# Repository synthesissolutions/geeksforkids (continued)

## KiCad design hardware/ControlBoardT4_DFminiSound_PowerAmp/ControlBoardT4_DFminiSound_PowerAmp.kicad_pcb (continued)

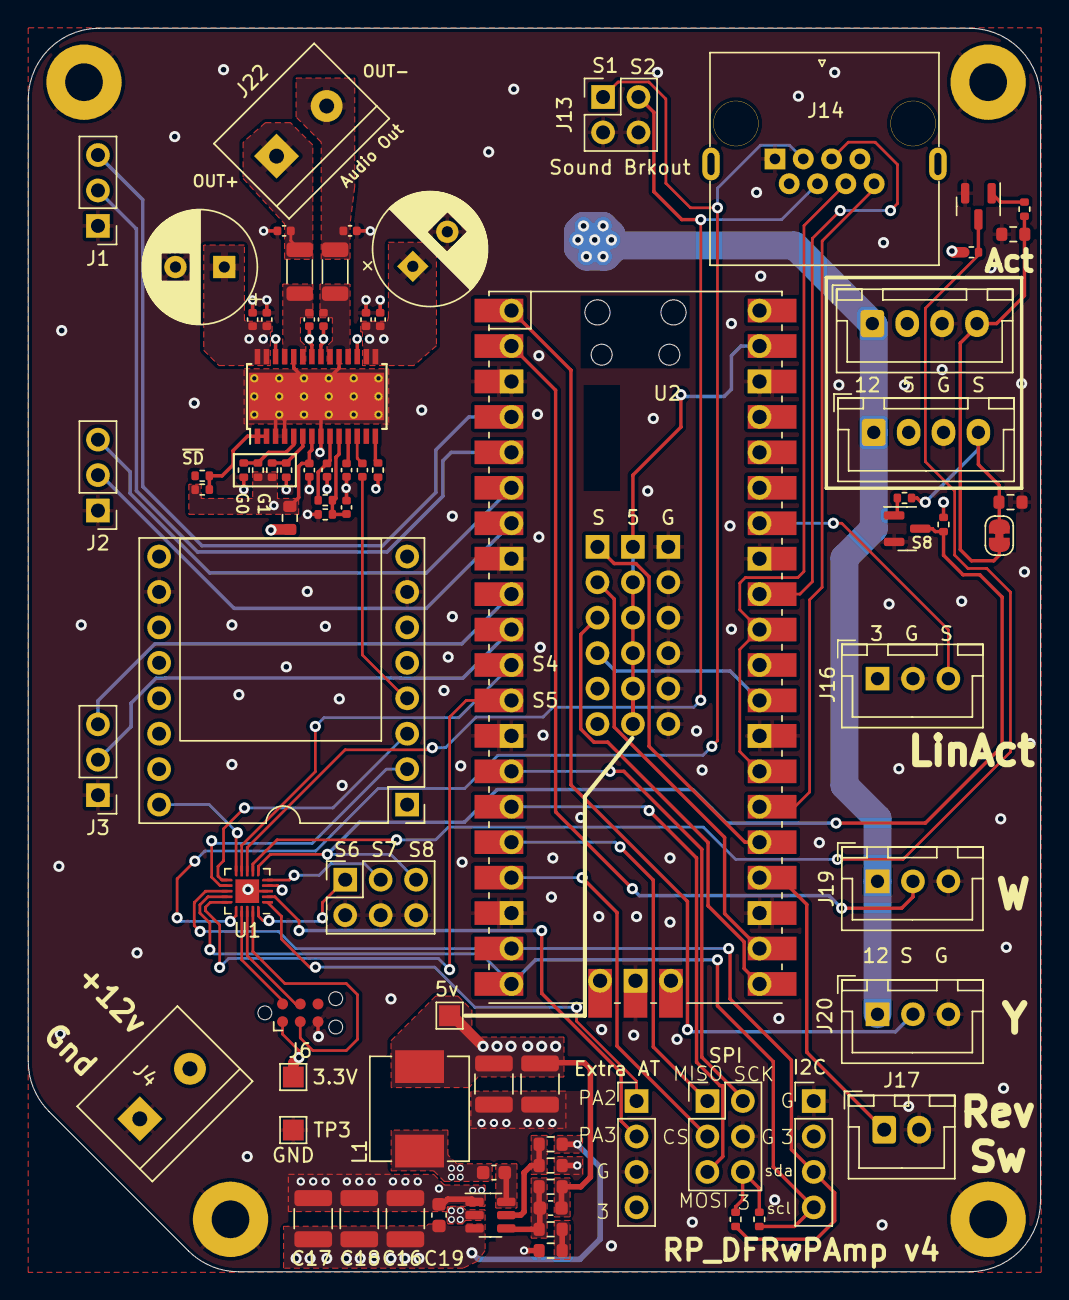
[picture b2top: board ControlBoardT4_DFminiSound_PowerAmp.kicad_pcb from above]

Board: 4 copper layers, 72.6 x 89.1 mm, 85 parts (0 on the bottom side), 68 nets.

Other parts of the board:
5v: 5V; TestPoint_Pad_1.5x1.5mm

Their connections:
+5V: 5v.1; also elsewhere on the board

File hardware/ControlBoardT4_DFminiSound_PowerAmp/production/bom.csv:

Designator,Footprint,Quantity,Value,LCSC Part #
"C1, C4, C5",0402,3,1uF,C1518208
"C10, C9",0402,2,0.47uF,C437527
"C11, C12, C15, C8",0402,4,1nF,C106205
"C13, C6",CP_Radial_D8.0mm_P3.50mm,2,100uF,C112510
"C14, C7",0402,2,100nF,C105882
"C16, C17, C18",1210,3,10µF,C380537
"C19, C20",0603,2,0.1µF,C77055
"C2, C3",0402,2,0.68uF,C113784
C21,0603,1,150pF,C527999
"C22, C23",1210,2,47µF,C77101
"FB1, FB2",1206,2,120Ohm@100MHz,C3011219
J15,PinSocket_1x06_P2.54mm_Vertical,1,RC_Signal,
J18,PinSocket_1x06_P2.54mm_Vertical,1,RC_5v,
J19,JST_XH_B3B-XH-A_1x03_P2.54mm_Vertical,1,M5 SCL,
J21,PinSocket_1x06_P2.54mm_Vertical,1,RC_GND,
L1,L_Sunlord_MWSA0603S,1,10µH,C132141
"Q1, Q2",SOT-23,2,2N7002,C8545
"R1, R12, R13, R17, R18, R8, R9",0402,7,100k,C60491
"R10, R11, R14",0402,3,0,C17168
R15,0603,1,10R,C22859
"R16, R5, R6",0402,3,1k,C11702
"R2, R4",0402,2,4.7k,C25900
R21,0603,1,100kΩ 1%,C25803
"R22, R3, R7",0603,3,13.3kΩ 1%,C25952
R23,0603,1,240Ω 1%,C23350
U1,VQFN-20-1EP_3x3mm_P0.4mm_EP1.7x1.7mm,1,ATtiny1616-M,C507118
U3,HTSSOP-28-1EP_4.4x9.7mm_P0.65mm_EP3.4x9.5mm_Mask2.4x6.17mm_ThermalVias,1,TPA3110D2,C30132
U4,SOT-23-6,1,TPS54302,C311983

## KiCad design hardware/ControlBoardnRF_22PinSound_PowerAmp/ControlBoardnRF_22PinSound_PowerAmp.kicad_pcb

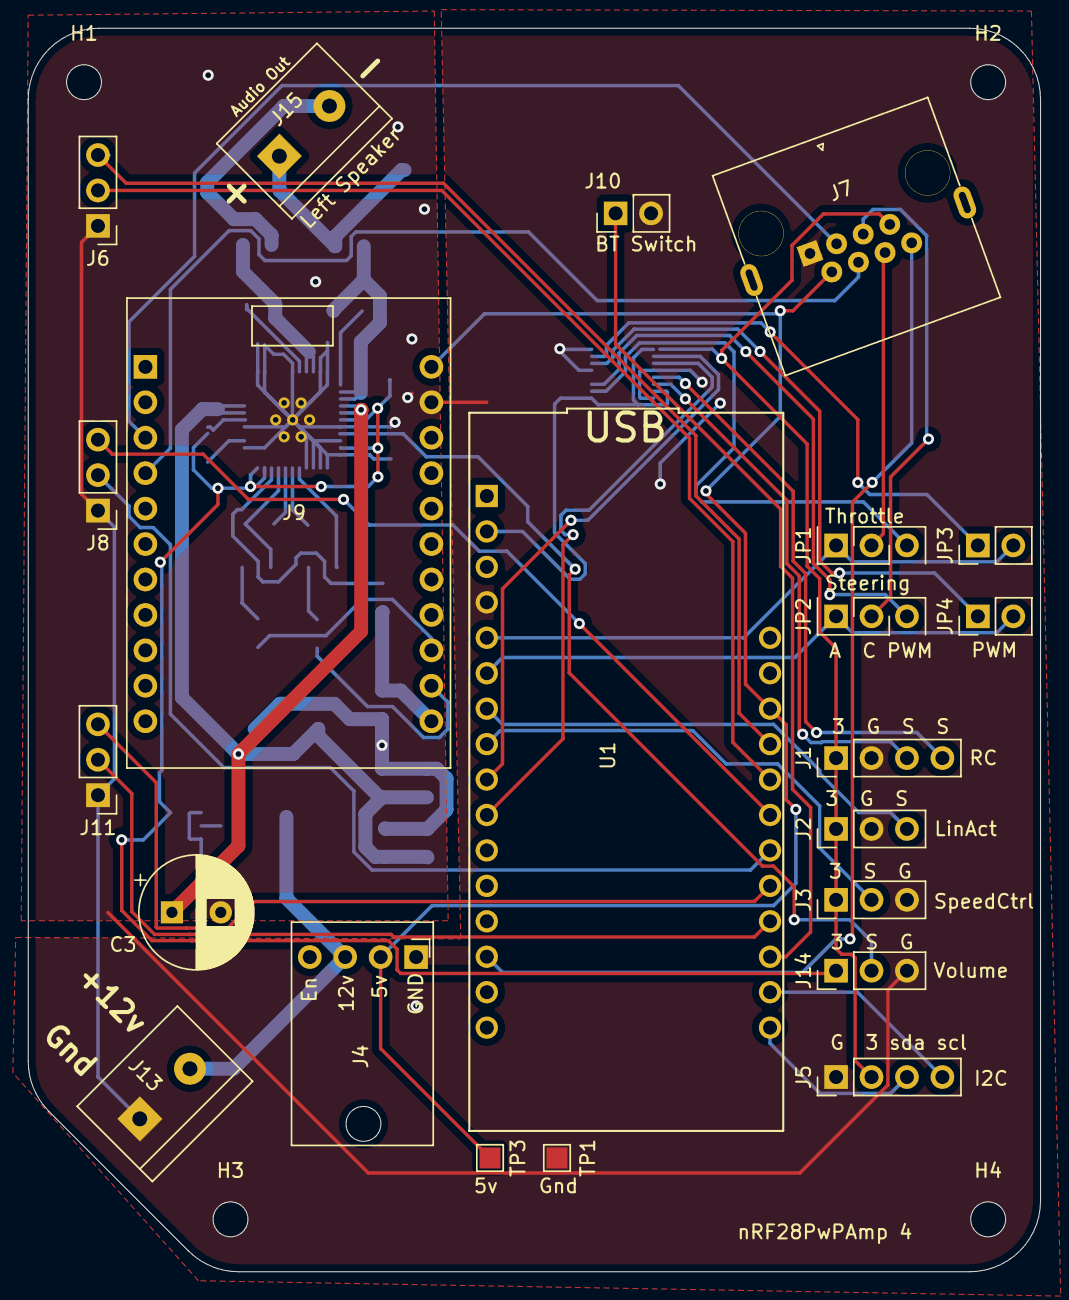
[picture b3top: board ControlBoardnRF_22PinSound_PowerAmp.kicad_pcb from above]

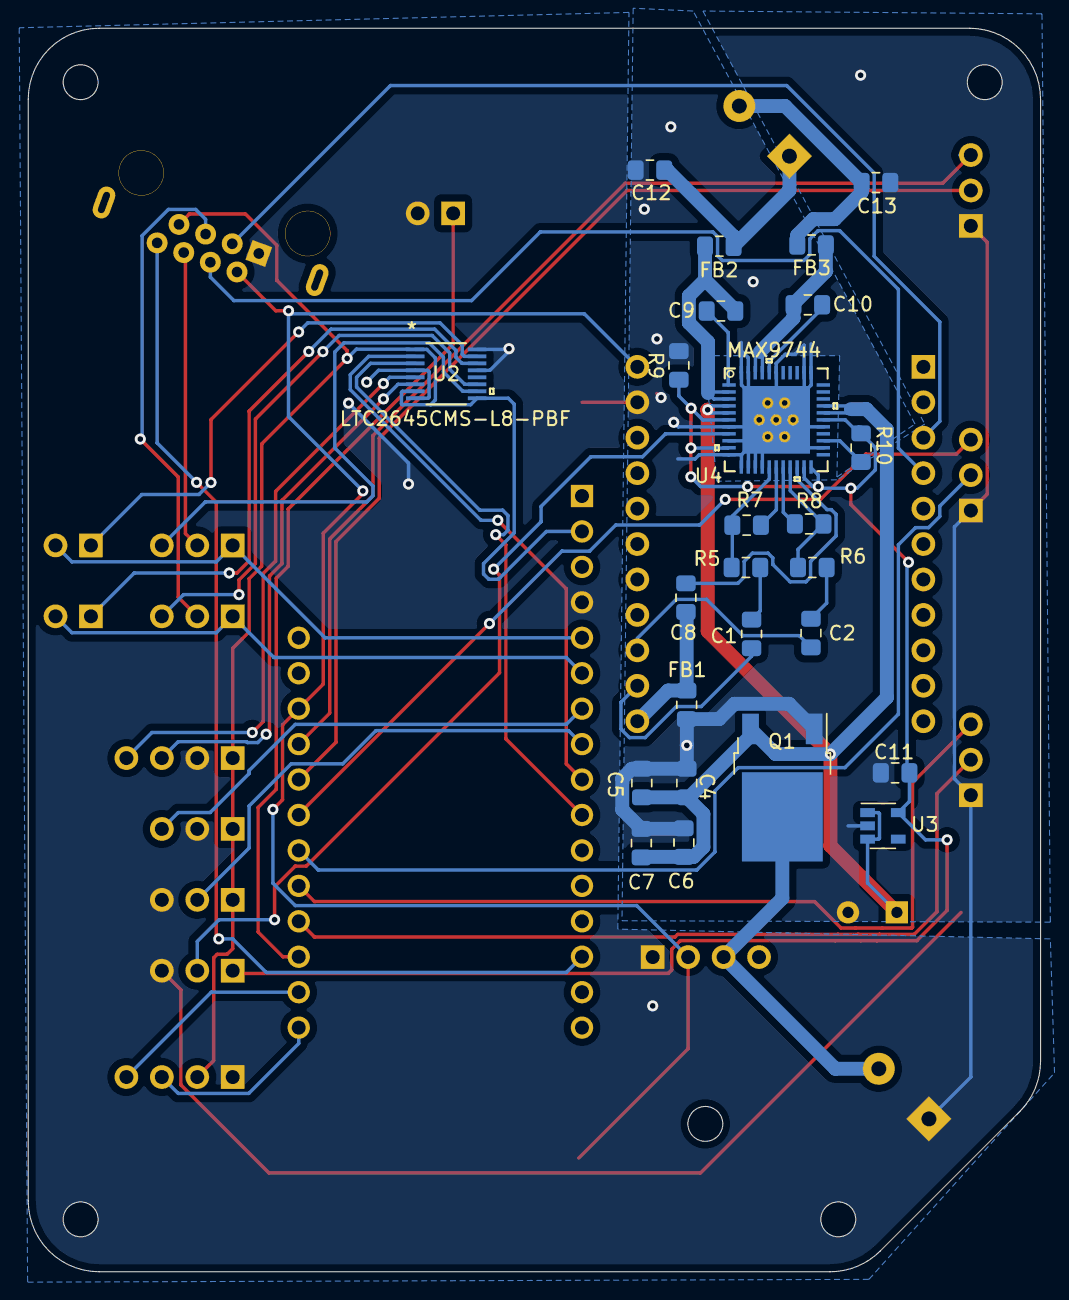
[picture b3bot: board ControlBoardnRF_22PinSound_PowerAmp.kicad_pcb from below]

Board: 2 copper layers, 72.6 x 89.1 mm, 51 parts (25 on the bottom side), 50 nets.

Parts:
C1, C2: 0.47µF; C_0805_2012Metric_Pad1.15x1.40mm_HandSolder
C3: 470µF; CP_Radial_D8.0mm_P3.50mm
C4, C5, C11: 10µF; C_0805_2012Metric_Pad1.15x1.40mm_HandSolder
C6, C7, C9, C10: 0.1µF; C_0805_2012Metric_Pad1.15x1.40mm_HandSolder
C8: 2.2µF; C_0805_2012Metric_Pad1.15x1.40mm_HandSolder
C12, C13: 470pF; C_0805_2012Metric_Pad1.15x1.40mm_HandSolder
FB1, FB2, FB3: MPZ2012S221AT00; L_0805_2012Metric_Pad1.15x1.40mm_HandSolder
H1, H2, H3, H4: MountingHole; MountingHole_2.5mm
J1: RC; PinHeader_1x04_P2.54mm_Vertical
J2: LinAct; PinHeader_1x03_P2.54mm_Vertical
J3: SpeedCtrl; PinHeader_1x03_P2.54mm_Vertical
J4: Power Input; AdaFruit_MPM3610
J5: I2C; PinHeader_1x04_P2.54mm_Vertical
J6: Left_M1; PinHeader_1x03_P2.54mm_Vertical
J7: 8P8C; RJ45_x08_Tab_Up
J8: Right_M2; PinHeader_1x03_P2.54mm_Vertical
J9: 22Pin_FXSound; FXSound_2x11_P2.54mm_Short
J10: BT Switch; PinHeader_1x02_P2.54mm_Vertical
J11: LinAct_M3; PinHeader_1x03_P2.54mm_Vertical
J13: Main Power; TerminalBlock_bornier-2_P5.08mm
J14: Volume; PinHeader_1x03_P2.54mm_Vertical
J15: Left Speaker; TerminalBlock_bornier-2_P5.08mm
JP1: Throttle Jumper; PinHeader_1x03_P2.54mm_Vertical
JP2: Steering Jumper; PinHeader_1x03_P2.54mm_Vertical
JP3: LTC Throttle Jumper; PinHeader_1x02_P2.54mm_Vertical
JP4: LTC Steering Jumper; PinHeader_1x02_P2.54mm_Vertical
Q1: AOD417; TO-252-2pin3D
R5, R6, R7, R8: 20K; R_0805_2012Metric_Pad1.15x1.40mm_HandSolder
R9, R10: 10K; R_0805_2012Metric_Pad1.15x1.40mm_HandSolder
TP1: Gnd; TestPoint_Pad_1.5x1.5mm
TP3: 5v; TestPoint_Pad_1.5x1.5mm
U1: Feather_nRF52840
U2: LTC2645CMS-L8-PBF
U3: AP2112K-3.3; SOT-23-5
U4: MAX9744; max9744eth&plus_Mod

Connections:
+3.3VP: C11.1, J14.1, R9.1, R10.2, U3.5, U4.6, U4.10, U4.21, U4.22, U4.28
+3V3: J1.1, J2.1, J3.1, J5.2, J7.7, U1.2, U2.1, U2.7, U2.9
+5V: J4.2, J7.2, J9.2, TP3.1, U1.26
+12V: J4.3, J13.2, Q1.3
ActiveSW: J7.8, U1.14
BT_Switch: J10.1, U1.19
GND: C3.2, C4.1, C5.1, C6.1, C7.1, C11.2, C12.1, C13.2, FB1.2, J1.2, J2.2, J3.3, J4.1, J5.1, J6.1, J7.1, J8.1, J9.4, J10.2, J11.1, J13.1, J14.3, Q1.1, R9.2, TP1.1, U1.4, U2.4, U2.8, U2.13, U2.16, U3.2, U4.7, U4.9, U4.11, U4.12, U4.13, U4.14, U4.15, U4.24, U4.27, U4.34, U4.35, U4.39, U4.43, U4.44, U4.45
GNDA: C8.2, FB1.1, J9.22
I2C_SCL: J5.4, U1.18
I2C_SDA: J5.3, U1.17
LeftIN: C1.2, J9.20
Left_DIR: J6.2, U1.24
Left_PWM: J6.3, U1.25
LinAct_DIR: J11.2, U1.20
LinAct_PWM: J11.3, U1.21
LinAct_Position: J2.3, U1.7
unnamed: C1.1, R5.2
unnamed: C2.1, R6.2
unnamed: C3.1, C4.2, C5.2, C6.2, C7.2, Q1.2, U3.1, U3.3, U4.4, U4.5, U4.29, U4.30
unnamed: C8.1, U4.20
unnamed: C9.1, FB2.1, U4.2, U4.3
unnamed: C9.2, U4.1
unnamed: C10.1, FB3.1, U4.41, U4.42
unnamed: C10.2, U4.40
unnamed: C12.2, FB2.2, J15.1
unnamed: C13.1, FB3.2, J15.2
unnamed: J7.5, JP2.2
unnamed: J7.6, JP1.2
unnamed: J14.2, U4.8
unnamed: JP3.1, U2.15
unnamed: JP4.1, U2.14
unnamed: R5.1, R7.2, U4.16
unnamed: R6.1, R8.2, U4.19
unnamed: R7.1, U4.17
unnamed: R8.1, U4.18
unnamed: R10.1, U4.25
PWMSteering: JP2.3, U2.11
PWMThrottle: JP1.3, U2.10
RCAnalogSteering: U1.10, U2.3
RCAnalogThrottle: U1.9, U2.2
RCPWMSteering: J1.4, U2.5
RCPWMThrottle: J1.3, U2.6
RightIN: C2.2, J9.18
Right_DIR: J8.2, U1.22
Right_PWM: J8.3, U1.23
Sound1: J7.3, J9.5
Sound2: J7.4, J9.7
SpeedCtrl: J3.2, U1.8
Steering: JP2.1, JP4.2, U1.6
Throttle: JP1.1, JP3.2, U1.5

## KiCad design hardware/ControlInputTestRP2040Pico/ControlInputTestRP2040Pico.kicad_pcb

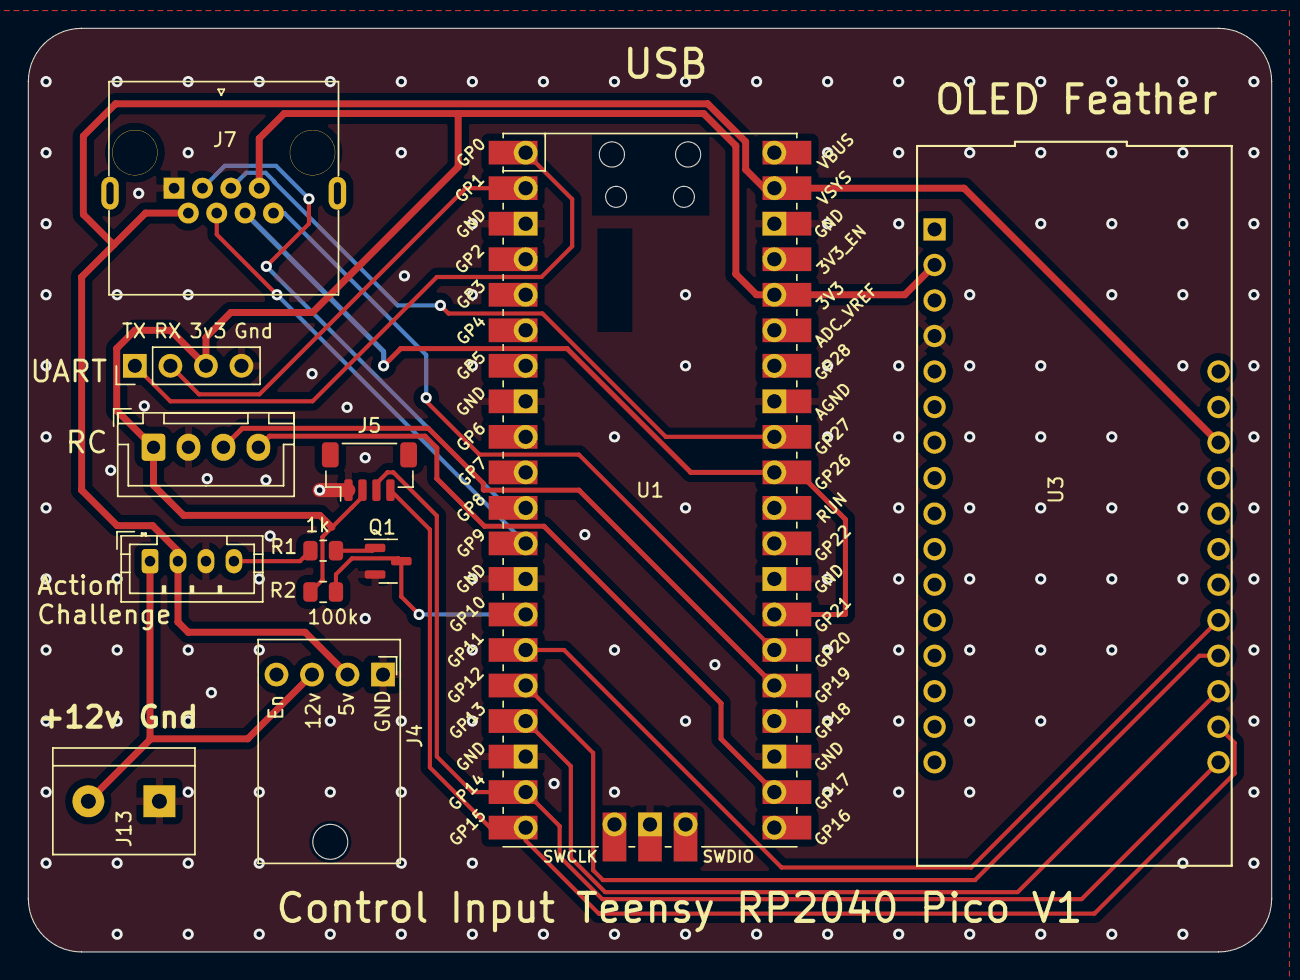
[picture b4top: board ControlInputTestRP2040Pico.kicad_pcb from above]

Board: 2 copper layers, 88.9 x 66.0 mm, 12 parts (0 on the bottom side), 21 nets.

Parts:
J1: RC; JST_XH_B4B-XH-A_1x04_P2.50mm_Vertical
J2: UART; PinHeader_1x04_P2.54mm_Vertical
J3: ActionChallenge; JST_PH_B4B-PH-K_1x04_P2.00mm_Vertical
J4: Power Input; AdaFruit_MPM3610
J5: I2C; JST_SH_BM04B-SRSS-TB_1x04-1MP_P1.00mm_Vertical
J7: 8P8C; RJ45_x08_Tab_Up
J13: Main Power; TerminalBlock_bornier-2_P5.08mm
Q1: Q_NMOS_GSD; SOT-23
R1: 1k; R_0805_2012Metric
R2: 100k; R_0805_2012Metric
U1: Pico; RPi_Pico_SMD_TH
U3: OLED Feather; Feather_nRF52840

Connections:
+3V3: J1.1, J2.3, J5.2, J7.7, R2.1, U1.36 (3V3), U3.2 (3V)
+5V: J3.2, J4.2, J7.2, U1.39 (VSYS), U3.26 (USB)
+12V: J3.1, J4.3, J13.2
ActionChallengeTrigger: Q1.3 (D), R2.2, U1.14 (GPIO10)
ActionSignal: J3.4, R1.1
ActiveSW: J7.8, U1.26 (GPIO20)
Button_A: U1.17 (GPIO13), U3.19 (5)
Button_B: U1.16 (GPIO12), U3.20 (6)
Button_C: U1.15 (GPIO11), U3.21 (9)
GND: J1.2, J2.4, J3.3, J4.1, J5.1, J7.1, J13.1, Q1.2 (S), U1.3 (GND), U1.8 (GND), U1.13 (GND), U1.18 (GND), U1.23 (GND), U1.28 (GND), U1.33 (AGND), U1.38 (GND), U1.42 (GND), U3.4 (Gnd)
I2C_SCL: J5.4, U1.20 (GPIO15), U3.18 (SCL)
I2C_SDA: J5.3, U1.19 (GPIO14), U3.17 (SDA)
unnamed: Q1.1 (G), R1.2
RCPWMSteering: J1.4, U1.22 (GPIO17)
RCPWMThrottle: J1.3, U1.25 (GPIO19)
RX: J2.2, U1.2 (GPIO1)
Sound_1: J7.3, U1.11 (GPIO8)
Sound_2: J7.4, U1.12 (GPIO9)
Steering: J7.5, U1.32 (GPIO27_ADC1)
TX: J2.1, U1.1 (GPIO0)
Throttle: J7.6, U1.27 (GPIO21), U1.31 (GPIO26_ADC0)

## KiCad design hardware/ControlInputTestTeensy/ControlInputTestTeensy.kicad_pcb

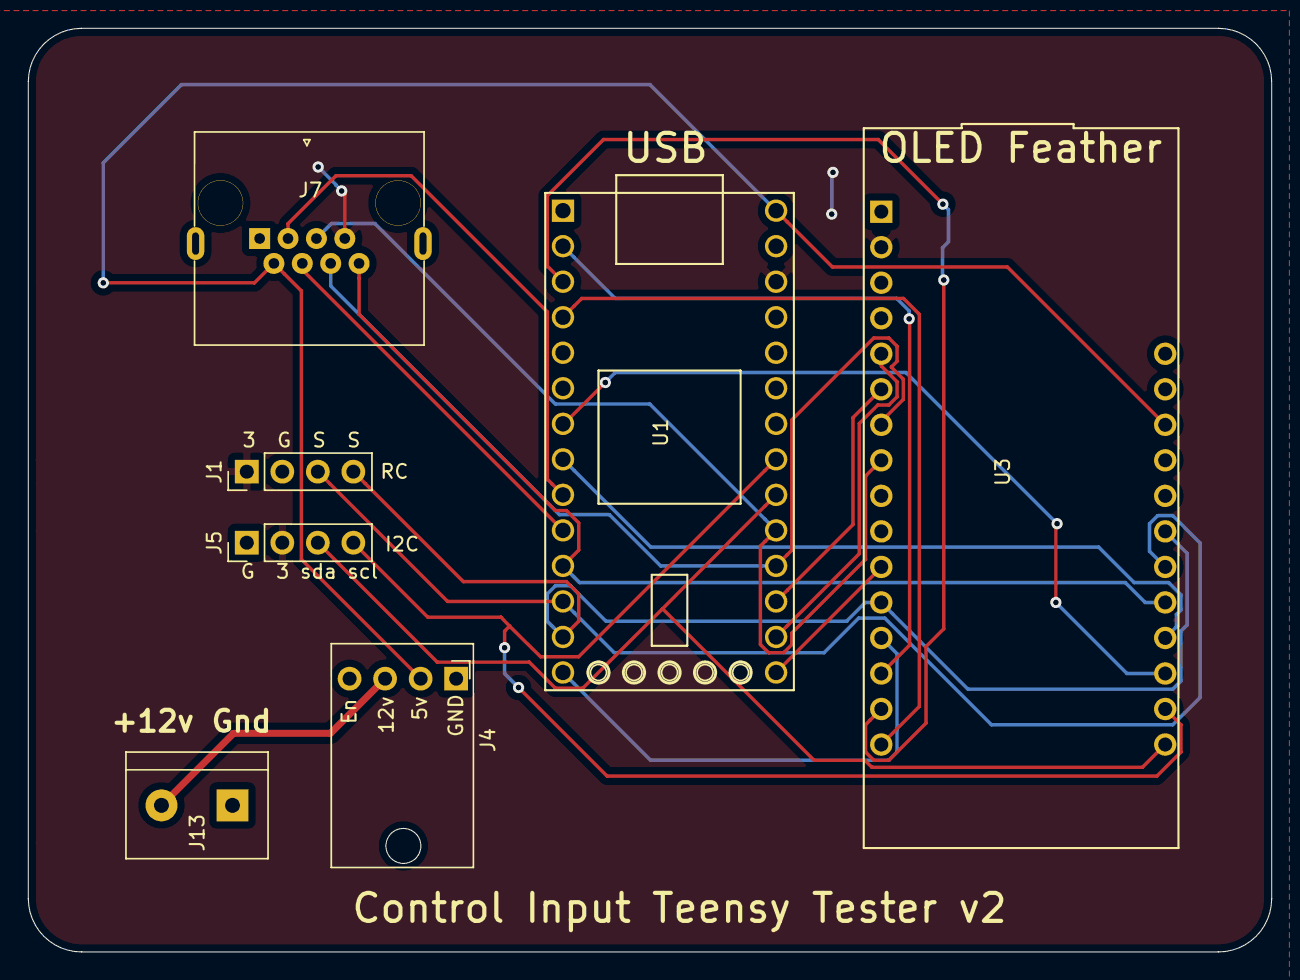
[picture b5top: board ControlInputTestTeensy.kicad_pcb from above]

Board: 2 copper layers, 88.9 x 66.0 mm, 7 parts (0 on the bottom side), 22 nets.

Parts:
J1: RC; PinHeader_1x04_P2.54mm_Vertical
J4: Power Input; AdaFruit_MPM3610
J5: I2C; PinHeader_1x04_P2.54mm_Vertical
J7: 8P8C; RJ45_x08_Tab_Up
J13: Main Power; TerminalBlock_bornier-2_P5.08mm
U1: Teensy4.0_NoMid; Teensy40_NoMid
U3: OLED Feather; Feather_nRF52840

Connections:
+3V3: J1.1, J5.2, J7.7, U1.26, U3.2
+5V: J4.2, J7.2, U1.28, U3.26
+12V: J4.3, J13.2
A0: U1.16, U3.5
A1: U1.17, U3.6
ActiveSW: J7.8, U1.11, U3.21
D2: U1.4, U3.16
D5: U1.7, U3.19
D6: U1.8, U3.20
D7: J7.3, U1.9
D8: J7.4, U1.10
GND: J1.2, J4.1, J5.1, J7.1, J13.1, U1.1, U1.27, U3.4
I2C_SCL: J5.4, U1.21, U3.18
I2C_SDA: J5.3, U1.20, U3.17
MI: U1.14, U3.13
RCPWMSteering: J1.4, U1.13, U3.12, U3.23
RCPWMThrottle: J1.3, U1.12, U3.22
RX: U1.2, U3.14
SCK: U1.15, U3.11
Steering: J7.5, U1.19, U3.8
TX: U1.3, U3.15
Throttle: J7.6, U1.18, U3.7

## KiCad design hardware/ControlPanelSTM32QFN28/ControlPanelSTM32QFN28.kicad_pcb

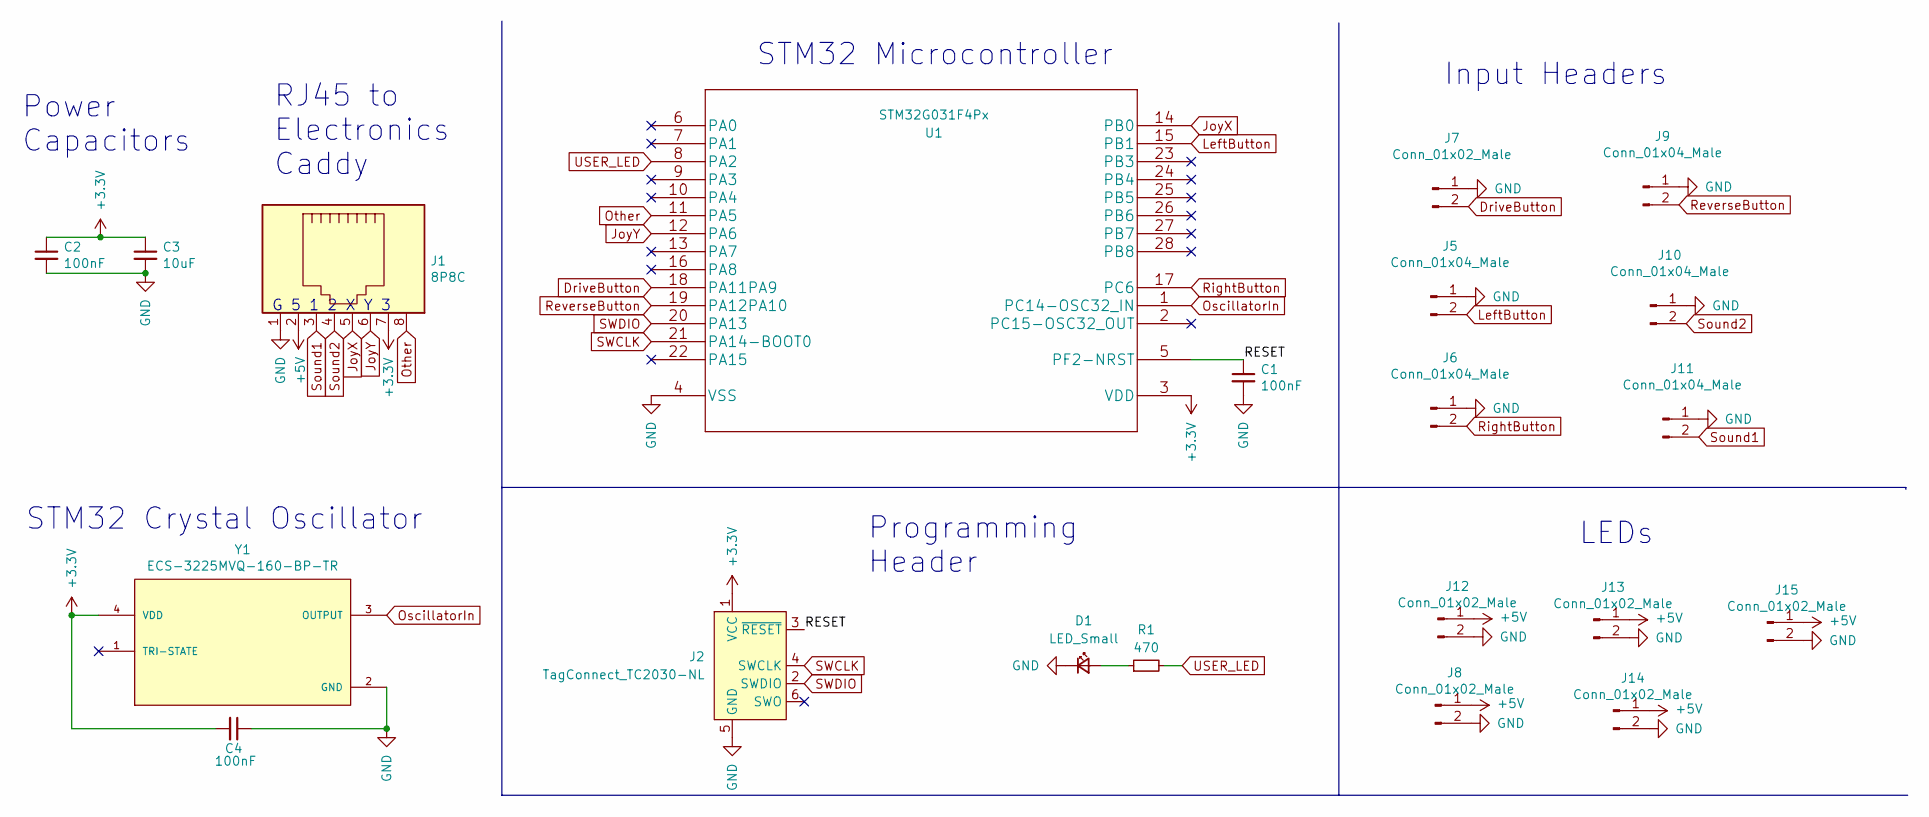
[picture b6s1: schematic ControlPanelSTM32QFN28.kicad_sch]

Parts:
C1, C2, C4: 100nF; C_0402_1005Metric; MPN C307331
C3: 10uF; C_0603_1608Metric; MPN C96446
D1: LED_Small; C_0603_1608Metric
J1: 8P8C; RJ45_x08_Tab_Up
J2: TagConnect_TC2030-NL; Tag-Connect_TC2030-IDC-NL_2x03_P1.27mm_Vertical
J5, J6, J9, J10, J11: Conn_01x04_Male; JST_XH_B2B-XH-A_1x02_P2.50mm_Vertical; MPN C158012
J7, J8, J12, J13, J14, J15: Conn_01x02_Male; JST_XH_B2B-XH-A_1x02_P2.50mm_Vertical; MPN C158012
R1: 470; C_0402_1005Metric; MPN C25117
U1: STM32G031F4Px; STM32G031G8U6; MPN C432211
Y1: ECS-3225MVQ-160-BP-TR; OSC_ECS-3225MVQ-160-BP-TR; MPN C252336

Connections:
+3V3: C2.1, C3.1, C4.2, J1.7, J2.1 (VCC), U1.3 (VDD), Y1.4 (VDD)
+5V: J1.2, J8.1, J12.1, J13.1, J14.1, J15.1
/RESET: C1.1, J2.3 (~RESET), U1.5 (PF2-NRST)
DriveButton: J7.2, U1.18 (PA11PA9)
GND: C1.2, C2.2, C3.2, C4.1, D1.1 (K), J1.1, J2.5 (GND), J5.1, J6.1, J7.1, J8.2, J9.1, J10.1, J11.1, J12.2, J13.2, J14.2, J15.2, U1.4 (VSS), Y1.2 (GND)
JoyX: J1.5, U1.14 (PB0)
JoyY: J1.6, U1.12 (PA6)
LeftButton: J5.2, U1.15 (PB1)
unnamed: D1.2 (A), R1.1
OscillatorIn: U1.1 (PC14-OSC32_IN), Y1.3 (OUTPUT)
Other: J1.8, U1.11 (PA5)
ReverseButton: J9.2, U1.19 (PA12PA10)
RightButton: J6.2, U1.17 (PC6)
SWCLK: J2.4 (SWCLK), U1.21 (PA14-BOOT0)
SWDIO: J2.2 (SWDIO), U1.20 (PA13)
Sound1: J1.3, J11.2
Sound2: J1.4, J10.2
USER_LED: R1.2, U1.8 (PA2)

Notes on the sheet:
STM32 Microcontroller
RJ45 to Electronics Caddy
LEDs
Programming Header
Power Capacitors
Input Headers
STM32 Crystal Oscillator
G 5 1 2 X Y 3

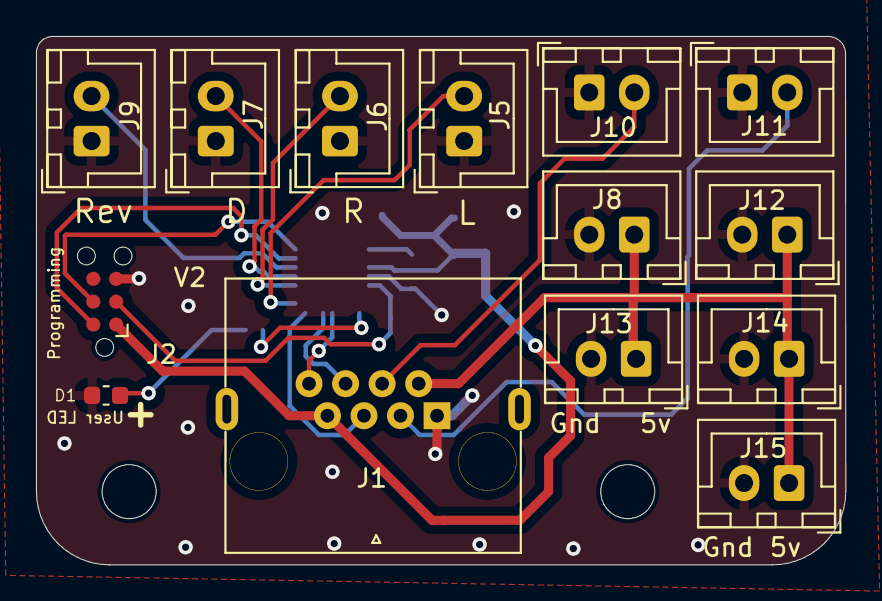
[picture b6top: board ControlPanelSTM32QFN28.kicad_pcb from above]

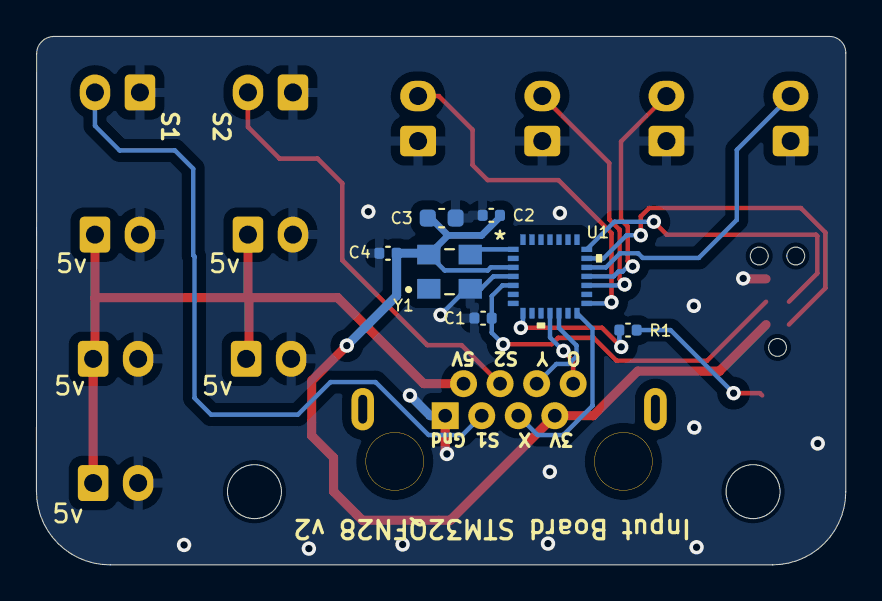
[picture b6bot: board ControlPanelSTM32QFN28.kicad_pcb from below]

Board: 2 copper layers, 45.0 x 29.4 mm, 21 parts (7 on the bottom side), 18 nets.

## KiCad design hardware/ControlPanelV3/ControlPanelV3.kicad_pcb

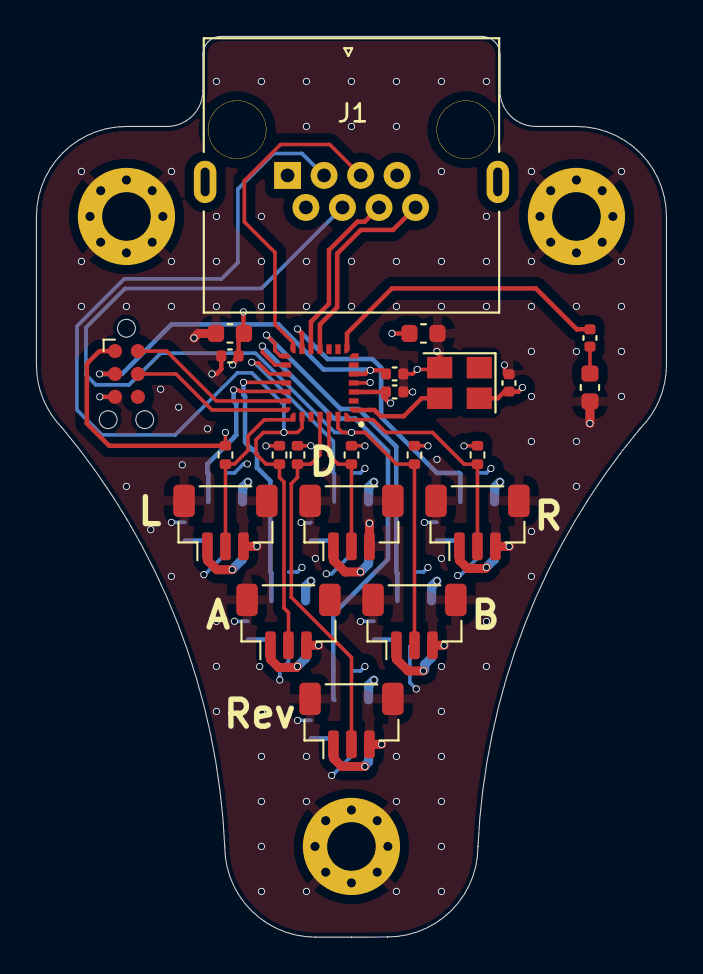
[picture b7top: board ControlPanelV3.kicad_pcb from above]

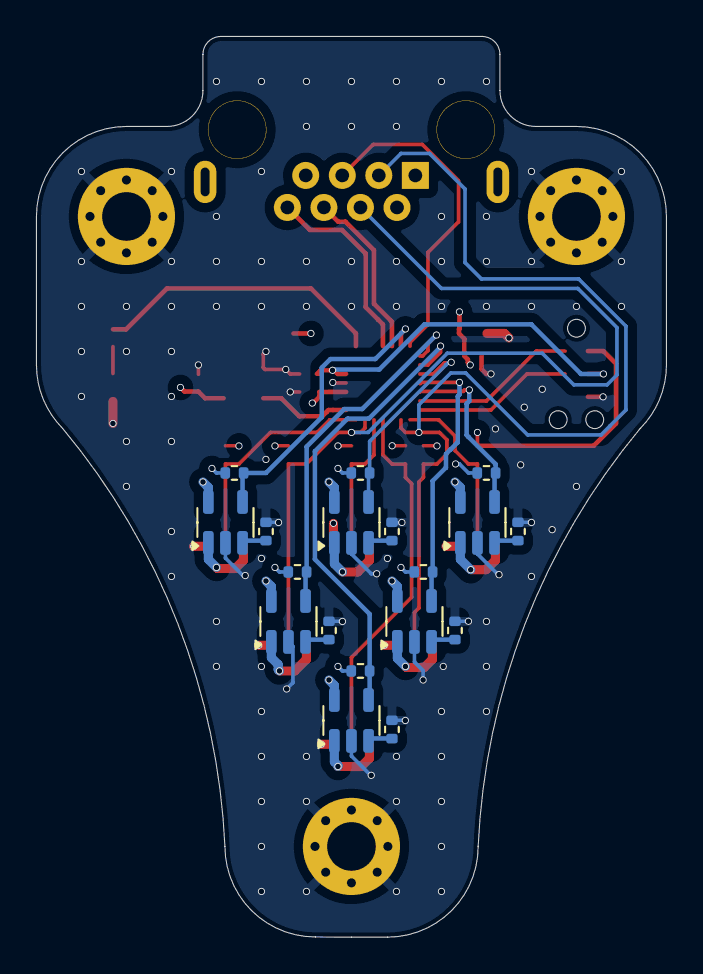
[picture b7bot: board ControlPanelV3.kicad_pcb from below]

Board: 4 copper layers, 35.0 x 50.0 mm, 45 parts (18 on the bottom side), 36 nets.

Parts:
C1, C2, C5, C6: 100nF; C_0402_1005Metric
C3, C4: 10uF; C_0603_1608Metric
D1: Red; C_0603_1608Metric
H1, H2, H3: M2.5; MountingHole_2.7mm_M2.5_Pad_Via
J1: 8P8C; RJ45_x08_Tab_Up
J2: TC2030; Tag-Connect_TC2030-IDC-NL_2x03_P1.27mm_Vertical
J3, J4, J5, J6, J7, J8: JST SH; JST_SH_BM03B-SRSS-TB_1x03-1MP_P1.00mm_Vertical
R1: 470Ω; C_0402_1005Metric
R2, R3, R4, R5, R6, R7, R8, R9, R10, R11, R12, R13, R14, R15, R16, R17, R18, R19: 10kΩ; R_0402_1005Metric
U1: UFQFPN-28; STM32G031G8U6
U2, U3, U4, U5, U6, U7: TPS2041B; SOT-23-5
Y1: 16MHz; Crystal_SMD_3225-4Pin_3.2x2.5mm

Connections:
+3V3: C2.1, C4.1, C6.2, J1.7, J2.1 (VCC), R2.1, R3.1, R4.1, R5.1, R6.1, R7.1, R11.1, R12.1, R13.1, R14.1, R15.1, R16.1, U1.3 (VDD), Y1.4 (V+)
+5V: C1.1, C3.1, J1.2, U2.5 (IN), U3.5 (IN), U4.5 (IN), U5.5 (IN), U6.5 (IN), U7.5 (IN)
/Output Connectors/DRIVE_LED: J4.1, U3.1 (OUT)
/Output Connectors/LEFT_LED: J3.1, U2.1 (OUT)
/Output Connectors/REVERSE_LED: J8.1, U7.1 (OUT)
/Output Connectors/RIGHT_LED: J5.1, U4.1 (OUT)
/Output Connectors/SOUND_A_LED: J6.1, U5.1 (OUT)
/Output Connectors/SOUND_B_LED: J7.1, U6.1 (OUT)
ACTIVE_SW: J1.8, U1.11 (PA5)
CLK_32kHZ_OUT: U1.1 (PC14-OSC32_IN), Y1.3 (OUT)
GND: C1.2, C2.2, C3.2, C4.2, C5.2, C6.1, D1.1 (K), H1.1, H2.1, H3.1, J1.1, J2.5 (GND), J3.3, J3.MP (MountPin), J4.3, J4.MP (MountPin), J5.3, J5.MP (MountPin), J6.3, J6.MP (MountPin), J7.3, J7.MP (MountPin), J8.3, J8.MP (MountPin), R8.2, R9.2, R10.2, R17.2, R18.2, R19.2, U1.4 (VSS), U2.2 (GND), U3.2 (GND), U4.2 (GND), U5.2 (GND), U6.2 (GND), U7.2 (GND), Y1.2 (GND)
JOY_X: J1.5, U1.14 (PB0)
JOY_Y: J1.6, U1.12 (PA6)
unnamed: D1.2 (A), R1.1
unnamed: R8.1, U2.3 (~OC)
unnamed: R9.1, U3.3 (~OC)
unnamed: R10.1, U4.3 (~OC)
unnamed: R17.1, U5.3 (~OC)
unnamed: R18.1, U6.3 (~OC)
unnamed: R19.1, U7.3 (~OC)
STATUS_LED: R1.2, U1.8 (PA2)
SWCLK: J2.4 (SWCLK), U1.21 (PA14-BOOT0)
SWDIO: J2.2 (SWDIO), U1.20 (PA13)
nDRIVE_BTN: J4.2, R5.2, U1.26 (PB6)
nDRIVE_LED_CTRL: R4.2, U1.17 (PC6), U3.4 (~EN)
nLEFT_BTN: J3.2, R3.2, U1.22 (PA15)
nLEFT_LED_CTRL: R2.2, U1.19 (PA12PA10), U2.4 (~EN)
nREVERSE_BTN: J8.2, R16.2, U1.25 (PB5)
nREVERSE_LED_CTRL: R15.2, U1.16 (PA8), U7.4 (~EN)
nRIGHT_BTN: J5.2, R7.2, U1.28 (PB8)
nRIGHT_LED_CTRL: R6.2, U1.13 (PA7), U4.4 (~EN)
nRST: C5.1, J2.3 (~RESET), U1.5 (PF2-NRST)
nSOUND_A_BTN: J1.3, J6.2, R12.2, U1.23 (PB3)
nSOUND_A_LED_CTRL: R11.2, U1.18 (PA11PA9), U5.4 (~EN)
nSOUND_B_BTN: J1.4, J7.2, R14.2, U1.27 (PB7)
nSOUND_B_LED_CTRL: R13.2, U1.15 (PB1), U6.4 (~EN)

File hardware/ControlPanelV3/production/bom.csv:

Designator,Footprint,Quantity,Value,LCSC Part #
"C1, C2, C5, C6",0402,4,100nF,C307331
"C3, C4",0603,2,10uF,C96446
D1,0603,1,Red,C965799
"J3, J4, J5, J6, J7, J8",JST_SH_BM03B-SRSS-TB_1x03-1MP_P1.00mm_Vertical,6,JST SH,C495538
R1,0402,1,470Ω,C25117
"R10, R11, R12, R13, R14, R15, R16, R17, R18, R19, R2, R3, R4, R5, R6, R7, R8, R9",0402,18,10kΩ,C25744
U1,STM32G031G8U6,1,UFQFPN-28,C432211
"U2, U3, U4, U5, U6, U7",SOT-23-5,6,TPS2041B,C387727
Y1,Crystal_SMD_3225-4Pin_3.2x2.5mm,1,16MHz,C5189452

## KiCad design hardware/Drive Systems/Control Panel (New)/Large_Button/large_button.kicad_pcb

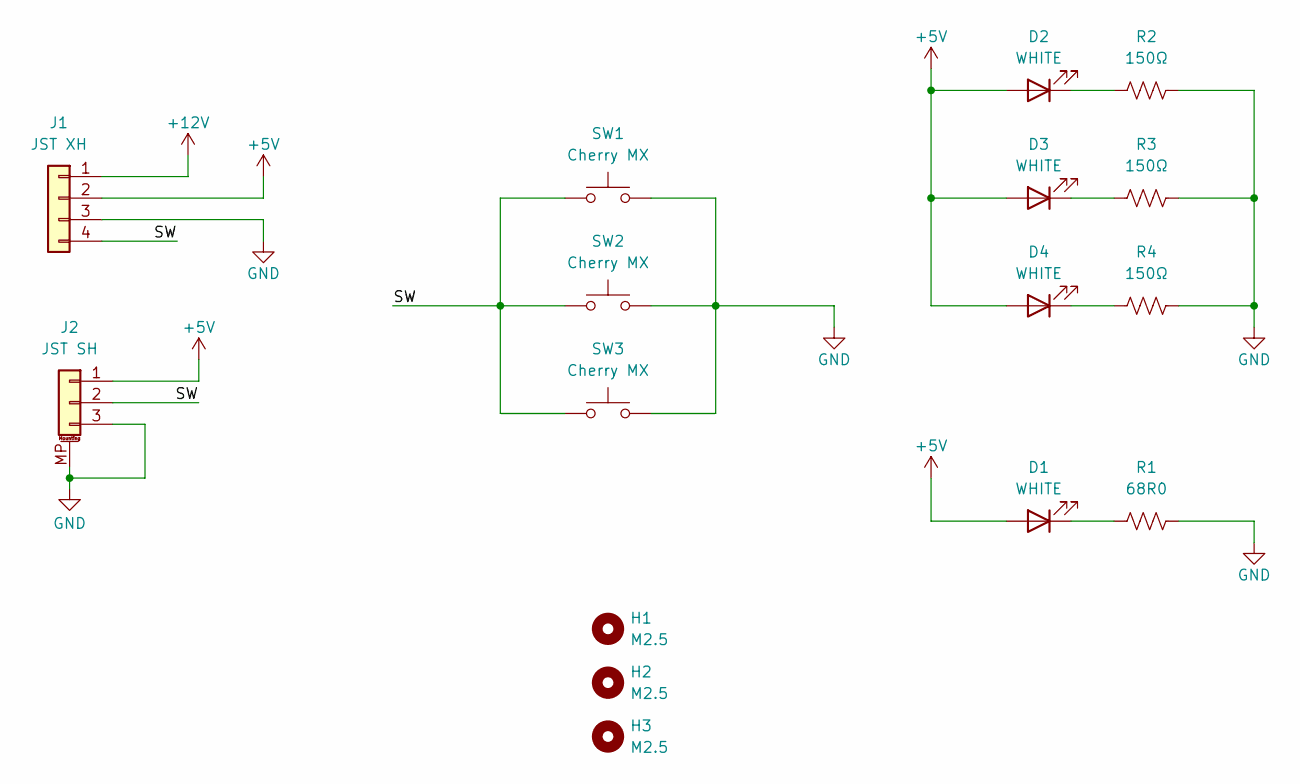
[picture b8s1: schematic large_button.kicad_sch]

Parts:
D1: WHITE; LED_PLCC_2835_Handsoldering; MPN C210322
D2, D3, D4: WHITE; LED_D3.0mm; MPN C210322
H1, H2, H3: M2.5; MountingHole_2.7mm_M2.5_DIN965
J1: JST XH; JST_XH_S4B-XH-A_1x04_P2.50mm_Horizontal; MPN C157925
J2: JST SH; JST_SH_SM03B-SRSS-TB_1x03-1MP_P1.00mm_Horizontal; MPN C160403
R1: 68R0; R_1210_3225Metric_Pad1.30x2.65mm_HandSolder; MPN C2930448
R2, R3, R4: 150Ω; R_0603_1608Metric; MPN C2907103
SW1, SW2, SW3: Cherry MX; SW_Cherry_MX_1.00u_PCB; MPN C400229

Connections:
+5V: D1.2 (A), D2.2 (A), D3.2 (A), D4.2 (A), J1.2, J2.1
+12V: J1.1
/SW: J1.4, J2.2, SW1.1, SW2.1, SW3.1
GND: J1.3, J2.3, J2.MP (MountPin), R1.2, R2.2, R3.2, R4.2, SW1.2, SW2.2, SW3.2
unnamed: D1.1 (K), R1.1
unnamed: D2.1 (K), R2.1
unnamed: D3.1 (K), R3.1
unnamed: D4.1 (K), R4.1

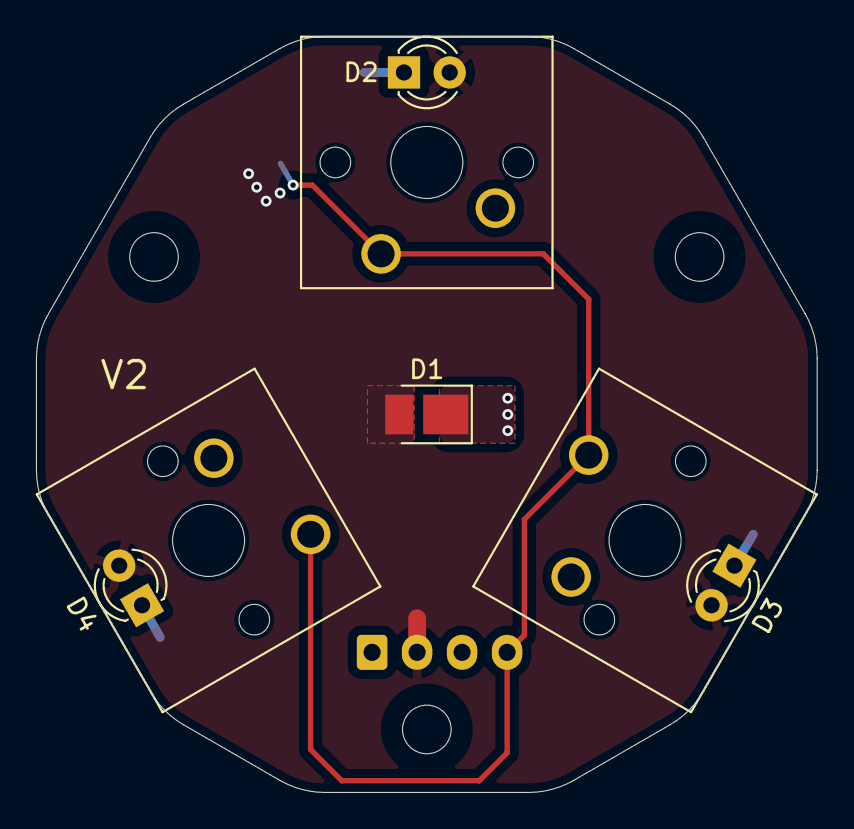
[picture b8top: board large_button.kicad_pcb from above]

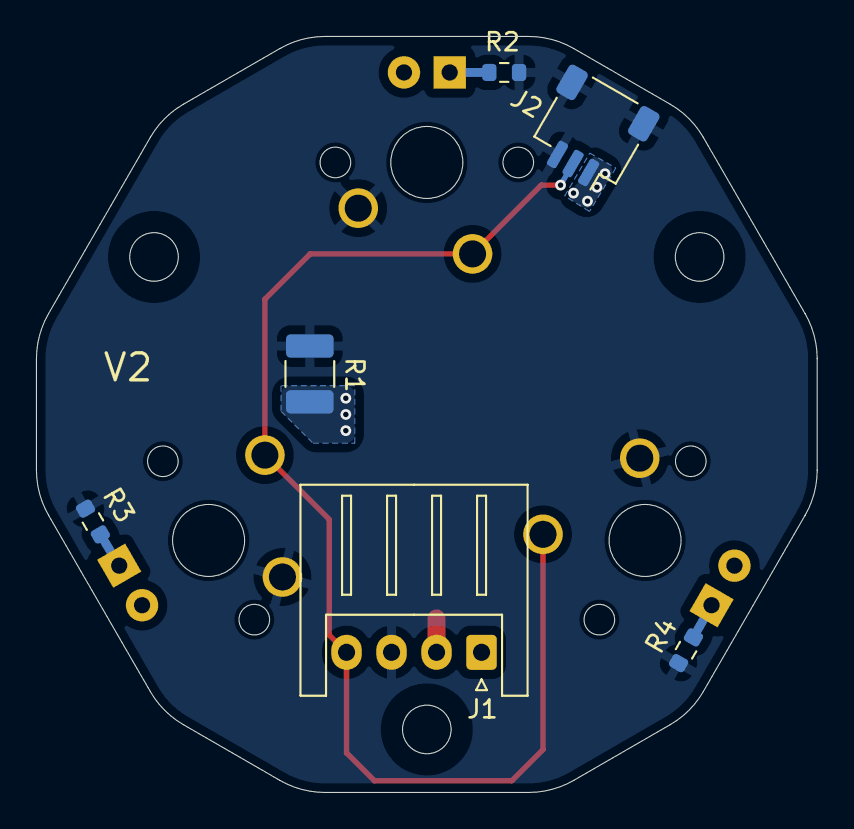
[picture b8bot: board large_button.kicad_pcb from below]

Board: 2 copper layers, 43.4 x 42.0 mm, 16 parts (6 on the bottom side), 7 nets.
